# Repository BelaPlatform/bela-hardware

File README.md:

# Bela Hardware

This repo contains the editable hardware design files for Bela products, including Bela, Bela Mini, Bela accessories.

These PCB designs have been created in and are editable with Cadsoft EAGLE (https://cadsoft.io) and Kicad (http://kicad.org). 

## Licensing

The hardware designs in this repo are licensed under a Creative Commons Attribution Sharealike license, or [CC-BY-SA](http://creativecommons.org/licenses/by-sa/3.0/). This means you are free edit and use these designs, as long as you agree to supply credit and release your results under the same license. [Read about CC-BY-SA here](http://creativecommons.org/licenses/by-sa/3.0/).

If you want to create a commercial product using the Bela hardware designs and don't want to release it under the same license, you will need a commercial license. Drop us an email at info@bela.io to discuss your project, and we can suggest a commercial license to fit your project's scope and scale.

## Branding

The Bela logo is copyrighted, and is reserved for products made or licensed by the Bela team. If you want to include a Bela logo on your project, we've made a Made With Bela logo just for this. [See this page for details on logo use](https://belaplatform.github.io/bela_sample/src/#logos) and to download the Made With Bela logo.

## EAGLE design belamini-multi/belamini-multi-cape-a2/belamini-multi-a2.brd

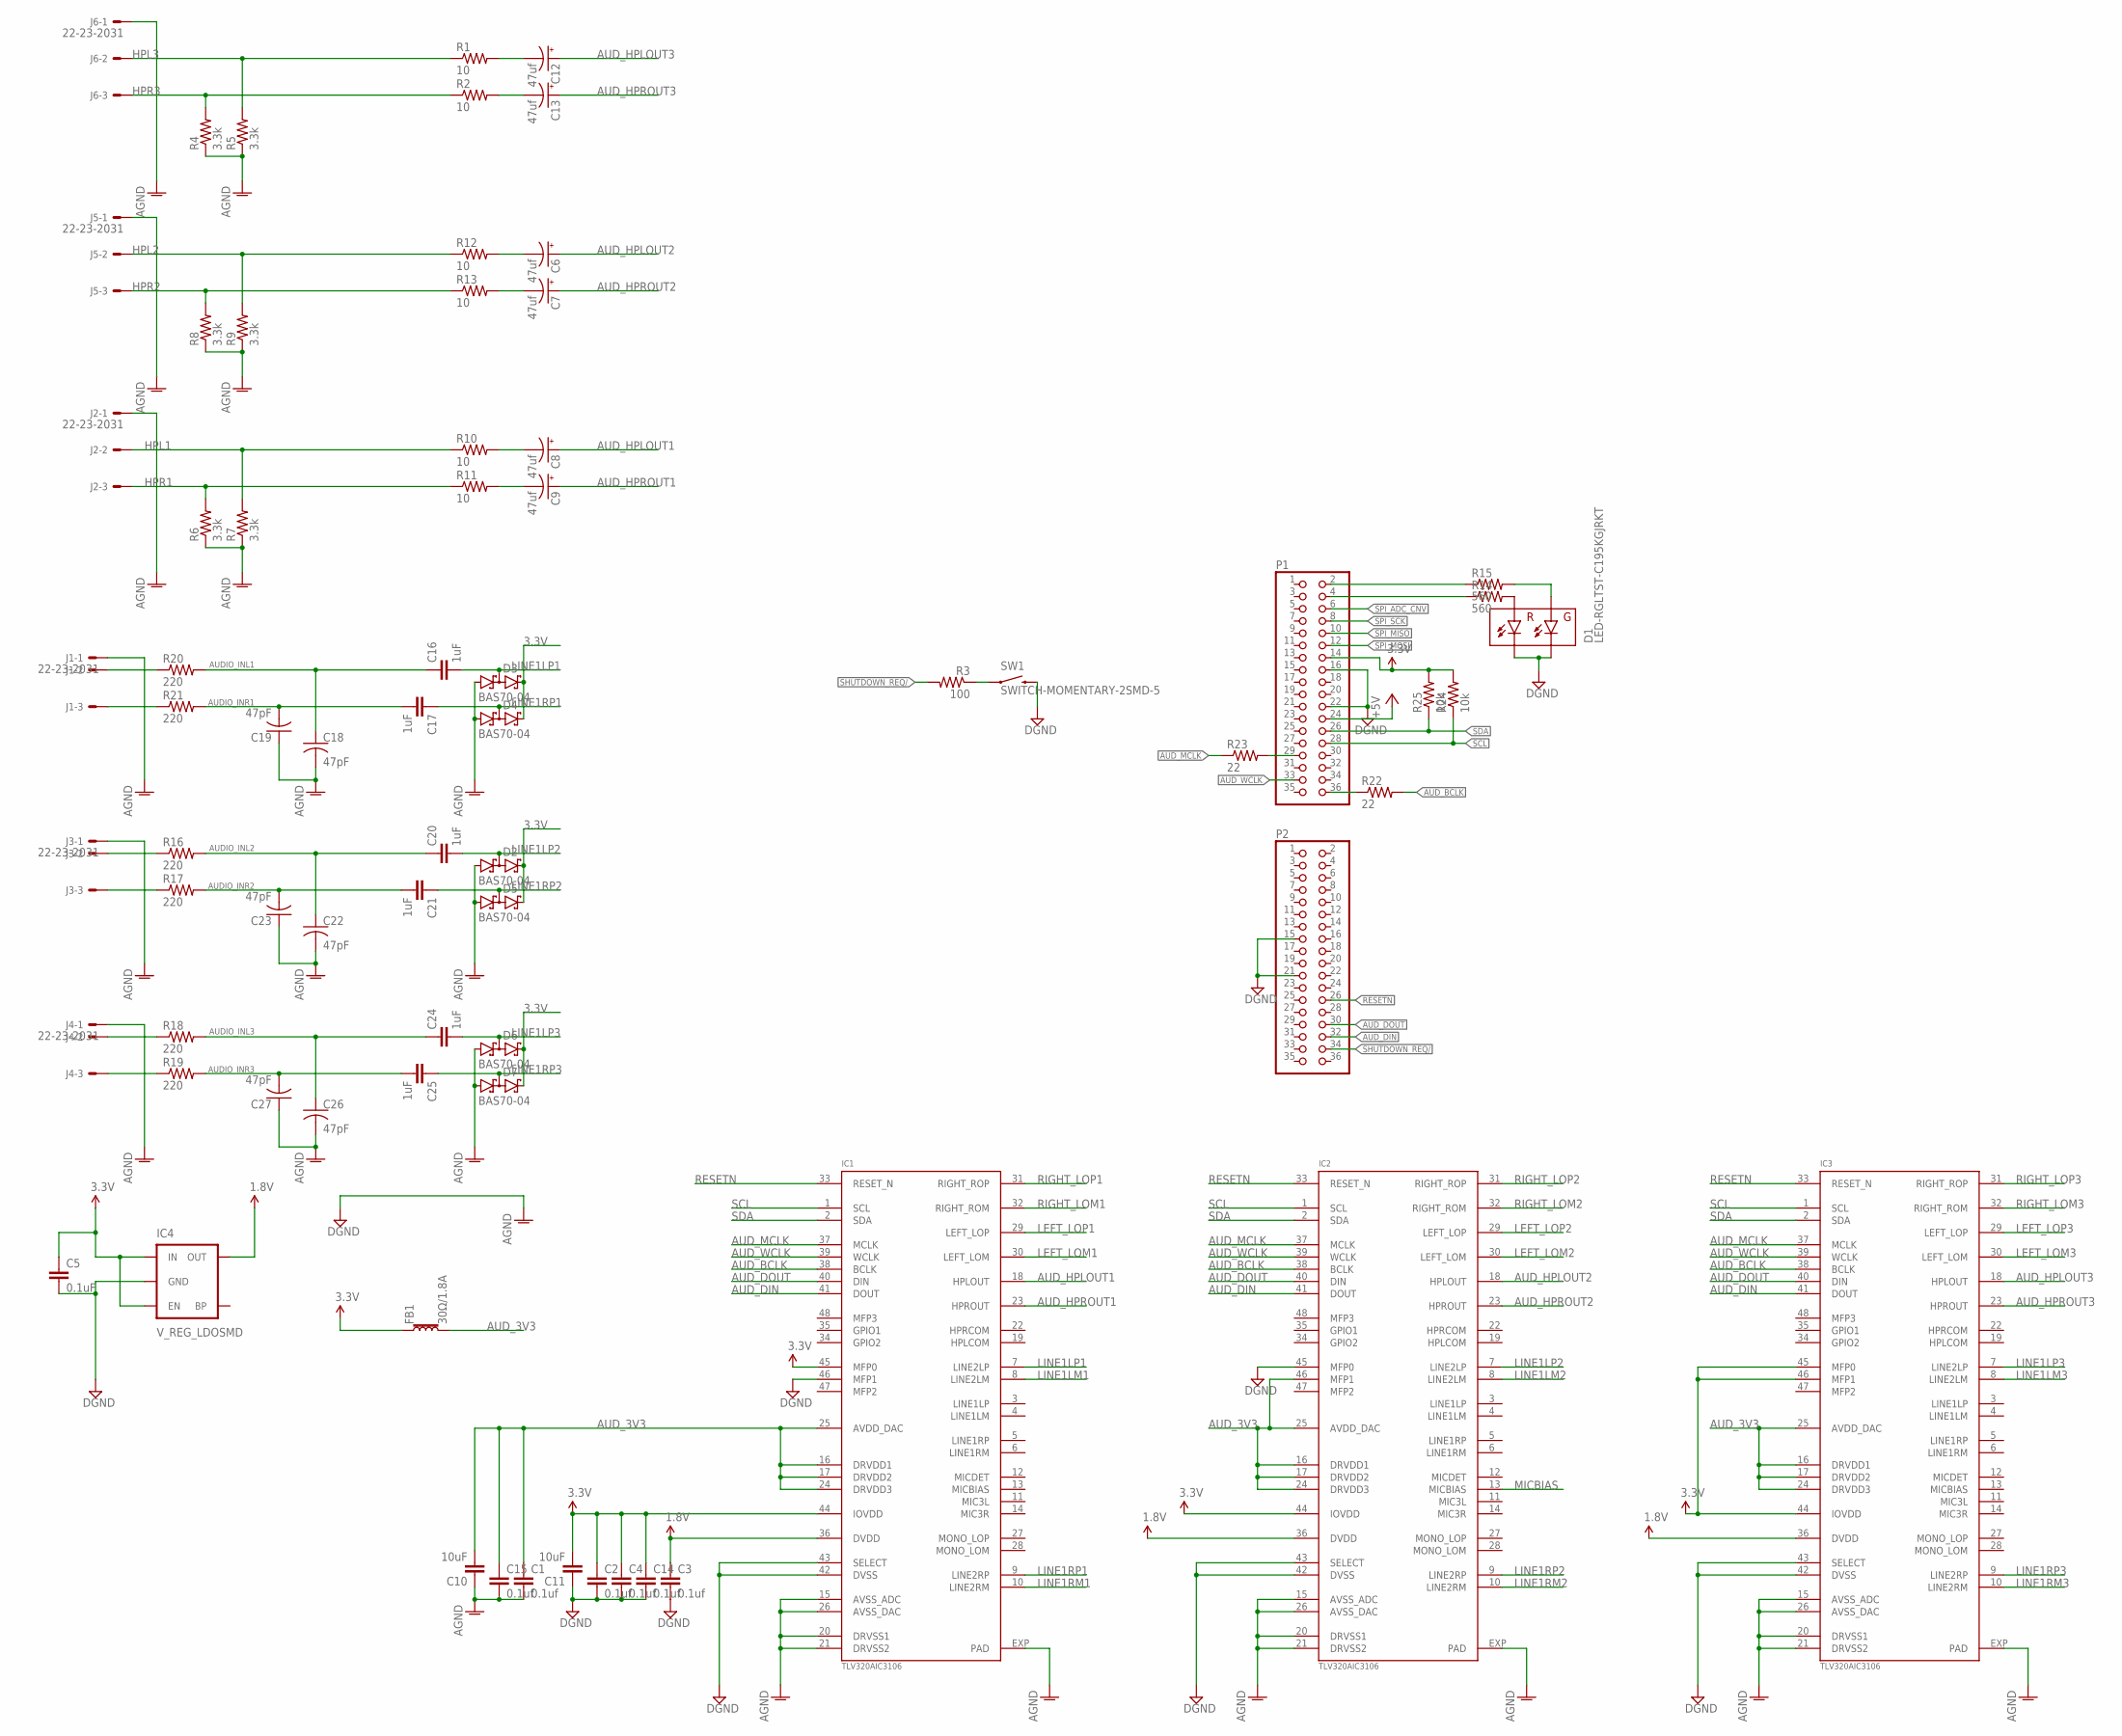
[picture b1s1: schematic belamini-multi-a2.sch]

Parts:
C1, C2, C3, C4, C14, C15: 0.1uf; C0603
C5: 0.1uF; C0603
C6, C7, C8, C9, C12, C13: 47uf; EIA3216
C10, C11: 10uF; 0603-CAP
C16, C17, C20, C21, C24, C25: 1uF; C0603
C18, C19, C22, C23, C26, C27: 47pF; C0402-SMALL
D1: LED-RGLTST-C195KGJRKT; LTST-C195KGJRKT
D2, D3, D4, D5, D6, D7: BAS70-04; SOT23
FB1: 30Ω/1.8A; 0603
IC1, IC2, IC3: TLV320AIC3106; QFN48
IC4: V_REG_LDOSMD; SOT23-5
J1, J2, J3, J4, J5, J6: 22-23-2031
P1, P2: PINHD-2X18; 2X18
R1, R2, R10, R11, R12, R13: 10; C0402-SMALL
R3: 100; C0402-SMALL
R4, R5, R6, R7, R8, R9: 3.3k; C0402-SMALL
R14, R15: 560; C0402-SMALL
R16, R17, R18, R19, R20, R21: 220; C0402-SMALL
R22, R23: 22; C0402-SMALL
R24, R25: 10k; C0402-SMALL
SW1: SWITCH-MOMENTARY-2SMD-5; TACTILE_SWITCH_SMD-4

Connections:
1.8V: C3.1, IC1.36 (DVDD), IC2.36 (DVDD), IC3.36 (DVDD), IC4.5 (OUT)
3.3V: C2.1, C4.1, C5.1, C11.2, C14.1, D2.2 (C2), D3.2 (C2), D4.2 (C2), D5.2 (C2), D6.2 (C2), D7.2 (C2), FB1.1, IC1.44 (IOVDD), IC1.45 (MFP0), IC2.44 (IOVDD), IC3.44 (IOVDD), IC3.45 (MFP0), IC3.46 (MFP1), IC4.1 (IN), IC4.3 (EN), P1.14, R24.P$2 (2), R25.P$2 (2)
+5V: P1.24
AGND: C1.2, C2.2, C3.2, C4.2, C5.2, C10.1, C11.1, C14.2, C15.2, C18.P$2 (2), C19.P$1 (1), C22.P$2 (2), C23.P$1 (1), C26.P$2 (2), C27.P$1 (1), D1.P$3 (GC), D1.P$4 (RC), D2.1 (A1), D3.1 (A1), D4.1 (A1), D5.1 (A1), D6.1 (A1), D7.1 (A1), IC1.15 (AVSS_ADC), IC1.20 (DRVSS1), IC1.21 (DRVSS2), IC1.26 (AVSS_DAC), IC1.42 (DVSS), IC1.43 (SELECT), IC1.46 (MFP1), IC1.EXP (PAD), IC2.15 (AVSS_ADC), IC2.20 (DRVSS1), IC2.21 (DRVSS2), IC2.26 (AVSS_DAC), IC2.42 (DVSS), IC2.43 (SELECT), IC2.45 (MFP0), IC2.EXP (PAD), IC3.15 (AVSS_ADC), IC3.20 (DRVSS1), IC3.21 (DRVSS2), IC3.26 (AVSS_DAC), IC3.42 (DVSS), IC3.43 (SELECT), IC3.EXP (PAD), IC4.2 (GND), J1.1, J2.1, J3.1, J4.1, J5.1, J6.1, P1.16, P1.22, P2.15, P2.21, R4.P$1 (1), R5.P$1 (1), R6.P$1 (1), R7.P$1 (1), R8.P$1 (1), R9.P$1 (1), SW1.4 (2)
AUDIO_INL1: C16.1, C18.P$1 (1), R20.P$2 (2)
AUDIO_INL2: C20.1, C22.P$1 (1), R16.P$2 (2)
AUDIO_INL3: C24.1, C26.P$1 (1), R18.P$2 (2)
AUDIO_INR1: C17.2, C19.P$2 (2), R21.P$2 (2)
AUDIO_INR2: C21.2, C23.P$2 (2), R17.P$2 (2)
AUDIO_INR3: C25.2, C27.P$2 (2), R19.P$2 (2)
AUD_3V3: C1.1, C10.2, C15.1, FB1.2, IC1.16 (DRVDD1), IC1.17 (DRVDD2), IC1.24 (DRVDD3), IC1.25 (AVDD_DAC), IC2.16 (DRVDD1), IC2.17 (DRVDD2), IC2.24 (DRVDD3), IC2.25 (AVDD_DAC), IC2.46 (MFP1), IC3.16 (DRVDD1), IC3.17 (DRVDD2), IC3.24 (DRVDD3), IC3.25 (AVDD_DAC)
AUD_BCLK: IC1.38 (BCLK), IC2.38 (BCLK), IC3.38 (BCLK), R22.P$2 (2)
AUD_DIN: IC1.41 (DOUT), IC2.41 (DOUT), IC3.41 (DOUT), P2.32
AUD_DOUT: IC1.40 (DIN), IC2.40 (DIN), IC3.40 (DIN), P2.30
AUD_HPLOUT1: C8.A (+), IC1.18 (HPLOUT)
AUD_HPLOUT2: C6.A (+), IC2.18 (HPLOUT)
AUD_HPLOUT3: C12.A (+), IC3.18 (HPLOUT)
AUD_HPROUT1: C9.A (+), IC1.23 (HPROUT)
AUD_HPROUT2: C7.A (+), IC2.23 (HPROUT)
AUD_HPROUT3: C13.A (+), IC3.23 (HPROUT)
AUD_MCLK: IC1.37 (MCLK), IC2.37 (MCLK), IC3.37 (MCLK), R23.P$1 (1)
AUD_WCLK: IC1.39 (WCLK), IC2.39 (WCLK), IC3.39 (WCLK), P1.33
HPL1: J2.2, R7.P$2 (2), R10.P$1 (1)
HPL2: J5.2, R9.P$2 (2), R12.P$1 (1)
HPL3: J6.2, R1.P$1 (1), R5.P$2 (2)
HPR1: J2.3, R6.P$2 (2), R11.P$1 (1)
HPR2: J5.3, R8.P$2 (2), R13.P$1 (1)
HPR3: J6.3, R2.P$1 (1), R4.P$2 (2)
LEFT_LOM1: IC1.30 (LEFT_LOM)
LEFT_LOM2: IC2.30 (LEFT_LOM)
LEFT_LOM3: IC3.30 (LEFT_LOM)
LEFT_LOP1: IC1.29 (LEFT_LOP)
LEFT_LOP2: IC2.29 (LEFT_LOP)
LEFT_LOP3: IC3.29 (LEFT_LOP)
LINE1LM1: IC1.8 (LINE2LM)
LINE1LM2: IC2.8 (LINE2LM)
LINE1LM3: IC3.8 (LINE2LM)
LINE1LP1: C16.2, D3.3 (C1A2), IC1.7 (LINE2LP)
LINE1LP2: C20.2, D2.3 (C1A2), IC2.7 (LINE2LP)
LINE1LP3: C24.2, D6.3 (C1A2), IC3.7 (LINE2LP)
LINE1RM1: IC1.10 (LINE2RM)
LINE1RM2: IC2.10 (LINE2RM)
LINE1RM3: IC3.10 (LINE2RM)
LINE1RP1: C17.1, D4.3 (C1A2), IC1.9 (LINE2RP)
LINE1RP2: C21.1, D5.3 (C1A2), IC2.9 (LINE2RP)
LINE1RP3: C25.1, D7.3 (C1A2), IC3.9 (LINE2RP)
MICBIAS: IC2.13 (MICBIAS)
unnamed: J1.2, R20.P$1 (1)
unnamed: C6.C (-), R12.P$2 (2)
unnamed: C7.C (-), R13.P$2 (2)
unnamed: J1.3, R21.P$1 (1)
unnamed: J3.2, R16.P$1 (1)
unnamed: D1.P$2 (RA), R14.P$2 (2)
unnamed: J3.3, R17.P$1 (1)
unnamed: C12.C (-), R1.P$2 (2)
unnamed: J4.2, R18.P$1 (1)
unnamed: C13.C (-), R2.P$2 (2)
unnamed: J4.3, R19.P$1 (1)
unnamed: D1.P$1 (GA), R15.P$2 (2)
unnamed: P1.4, R14.P$1 (1)
unnamed: P1.2, R15.P$1 (1)
unnamed: P1.29, R23.P$2 (2)
unnamed: P1.36, R22.P$1 (1)
unnamed: C8.C (-), R10.P$2 (2)
unnamed: R3.P$1 (1), SW1.1
unnamed: C9.C (-), R11.P$2 (2)
RESETN: IC1.33 (RESET_N), IC2.33 (RESET_N), IC3.33 (RESET_N), P2.26
RIGHT_LOM1: IC1.32 (RIGHT_ROM)
RIGHT_LOM2: IC2.32 (RIGHT_ROM)
RIGHT_LOM3: IC3.32 (RIGHT_ROM)
RIGHT_LOP1: IC1.31 (RIGHT_ROP)
RIGHT_LOP2: IC2.31 (RIGHT_ROP)
RIGHT_LOP3: IC3.31 (RIGHT_ROP)
SCL: IC1.1 (SCL), IC2.1 (SCL), IC3.1 (SCL), P1.28, R24.P$1 (1)
SDA: IC1.2 (SDA), IC2.2 (SDA), IC3.2 (SDA), P1.26, R25.P$1 (1)
SHUTDOWN_REQ/: P2.34, R3.P$2 (2)
SPI_ADC_CNV: P1.6
SPI_MISO: P1.10
SPI_MOSI: P1.12
SPI_SCK: P1.8

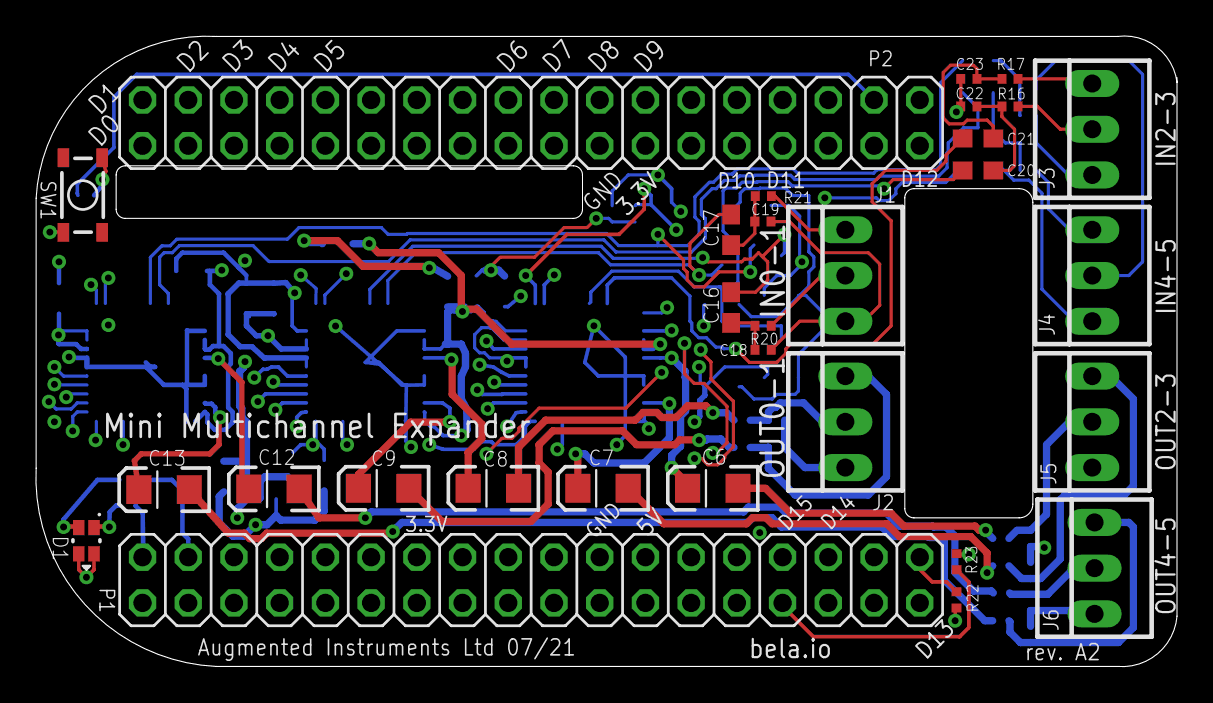
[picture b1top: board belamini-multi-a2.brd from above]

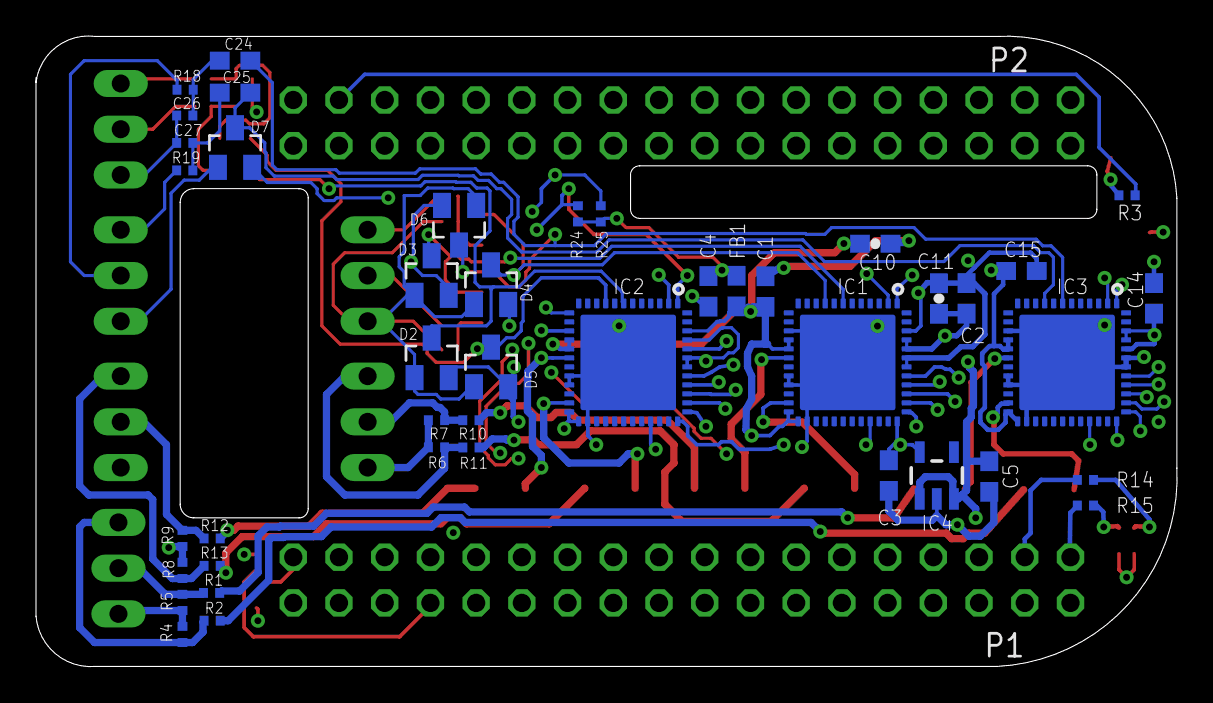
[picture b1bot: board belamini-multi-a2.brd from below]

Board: 4 copper layers, 63.4 x 35.0 mm, 73 parts (43 on the bottom side), 56 nets.

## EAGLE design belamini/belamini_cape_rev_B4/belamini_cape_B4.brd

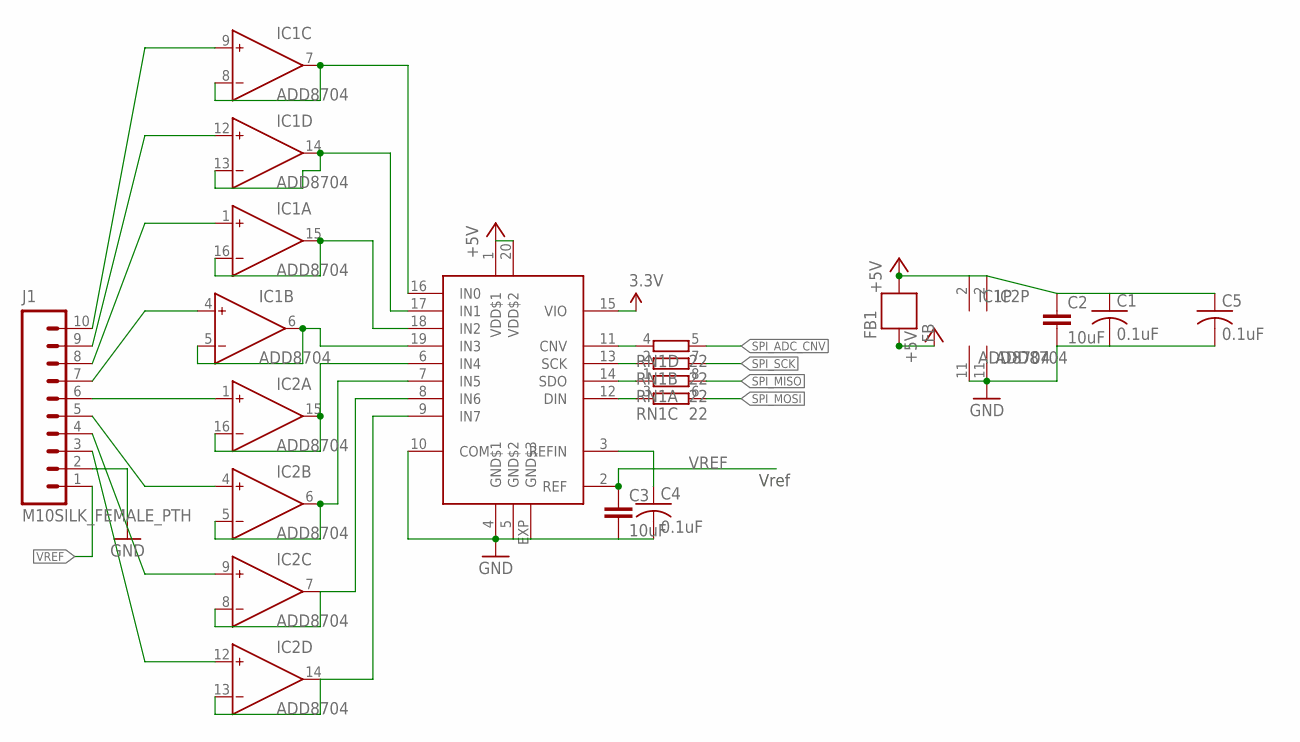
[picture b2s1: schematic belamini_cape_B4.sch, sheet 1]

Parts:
C1, C4, C5: 0.1uF; C0603
C2, C3: 10uF; 0603-CAP
FB1: FB; 0603
IC1, IC2: ADD8704; QFN16-3X3
IC3: AD7699; LFCSP20-LEADS
J1: M10SILK_FEMALE_PTH; 1X10
RN1: 22; 0603-ARC

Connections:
3.3V: IC3.15 (VIO); also elsewhere on the board
+5V_ADC_DAC: C1.1, C2.1, C5.1, FB1.1, IC1.2 (V+), IC2.2 (V+), IC3.1 (VDD$1), IC3.20 (VDD$2)
+5V_SYS: FB1.2; also elsewhere on the board
GND: C1.2, C2.2, C3.2, C4.2, C5.2, IC1.11 (V-), IC2.11 (V-), IC3.4 (GND$1), IC3.5 (GND$2), IC3.10 (COM), IC3.EXP (GND$3), J1.2; also elsewhere on the board
unnamed: IC2.1 (IN+), J1.6
unnamed: IC1.7 (OUT), IC1.8 (IN-), IC3.16 (IN0)
unnamed: IC1.13 (IN-), IC1.14 (OUT), IC3.17 (IN1)
unnamed: IC2.15 (OUT), IC2.16 (IN-), IC3.6 (IN4)
unnamed: IC2.5 (IN-), IC2.6 (OUT), IC3.7 (IN5)
unnamed: IC2.7 (OUT), IC2.8 (IN-), IC3.8 (IN6)
unnamed: IC2.13 (IN-), IC2.14 (OUT), IC3.9 (IN7)
unnamed: IC3.11 (CNV), RN1.4 (1)
unnamed: IC3.12 (DIN), RN1.3 (1)
unnamed: C4.1, IC3.3 (REFIN)
unnamed: IC3.13 (SCK), RN1.2 (1)
unnamed: IC3.14 (SDO), RN1.1
unnamed: IC1.5 (IN-), IC1.6 (OUT), IC3.19 (IN3)
unnamed: IC1.15 (OUT), IC1.16 (IN-), IC3.18 (IN2)
unnamed: IC1.9 (IN+), J1.10
unnamed: IC1.12 (IN+), J1.9
unnamed: IC1.1 (IN+), J1.8
unnamed: IC1.4 (IN+), J1.7
unnamed: IC2.4 (IN+), J1.5
unnamed: IC2.9 (IN+), J1.4
unnamed: IC2.12 (IN+), J1.3
SPI_ADC_CNV: RN1.5 (2); also elsewhere on the board
SPI_MISO: RN1.8 (2); also elsewhere on the board
SPI_MOSI: RN1.6 (2); also elsewhere on the board
SPI_SCK: RN1.7 (2); also elsewhere on the board
VREF: C3.1, IC3.2 (REF), J1.1

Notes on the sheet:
Vref

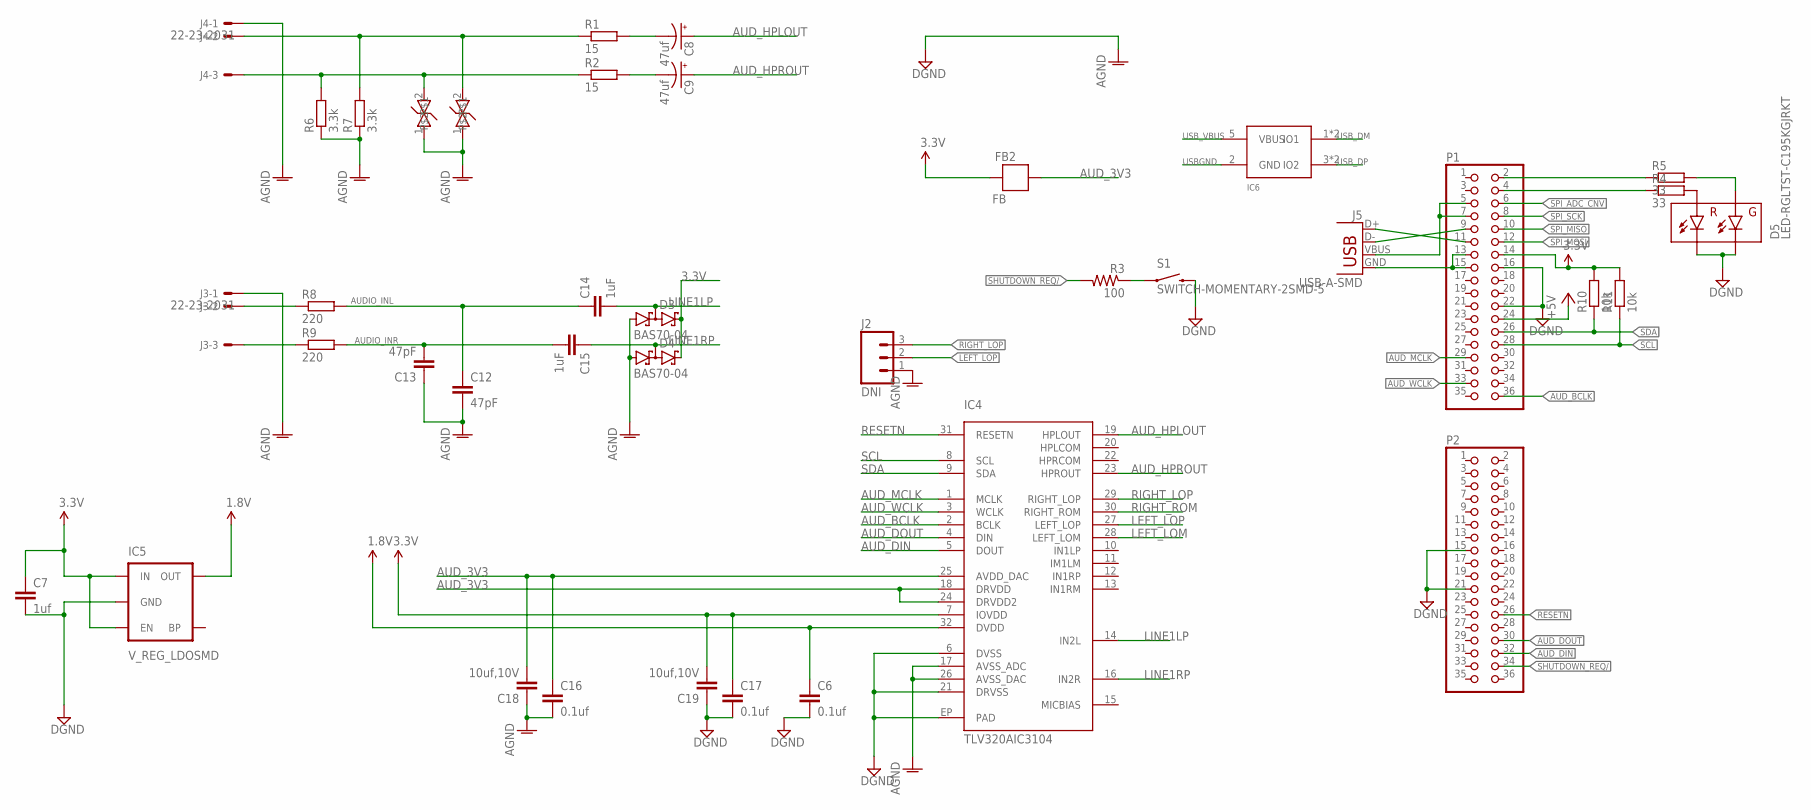
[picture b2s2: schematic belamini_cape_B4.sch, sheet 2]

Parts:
C6, C16, C17: 0.1uf; C0603
C7: 1uf; C0603
C8, C9: 47uf; EIA3216
C12, C13: 47pF; C0603
C14, C15: 1uF; C0603
C18, C19: 10uf,10V; 0603-CAP
D1, D2: PGB0010603MR; 0603
D3, D4: BAS70-04; SOT23
D5: LED-RGLTST-C195KGJRKT; LTST-C195KGJRKT
FB2: FB; 0603
IC4: TLV320AIC3104; QFN-32
IC5: V_REG_LDOSMD; SOT23-5
IC6: USBLC6-2; SOT23-6
J2: DNI; 1X03
J3, J4: 22-23-2031
J5: USB-A-SMD; USB-A-S-NOSILK-FEMALE
P1, P2: PINHD-2X18; 2X18
R1, R2: 15; R0603
R3: 100; R0603
R4, R5: 33; R0603
R6, R7: 3.3k; R0603
R8, R9: 220; R0603
R10, R11: 10k; R0603
S1: SWITCH-MOMENTARY-2SMD-5; TACTILE_SWITCH_SMD-4

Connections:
1.8V: C6.1, IC4.32 (DVDD), IC5.5 (OUT)
3.3V: C7.1, C17.1, C19.2, D3.2 (C2), D4.2 (C2), FB2.2, IC4.7 (IOVDD), IC5.1 (IN), IC5.3 (EN), P1.14, R10.2, R11.2; also elsewhere on the board
+5V_SYS: P1.24; also elsewhere on the board
AUDIO_INL: C12.1, C14.1, R8.2
AUDIO_INR: C13.2, C15.2, R9.2
AUD_3V3: C16.1, C18.2, FB2.1, IC4.18 (DRVDD), IC4.24 (DRVDD2), IC4.25 (AVDD_DAC)
AUD_BCLK: IC4.2 (BCLK), P1.36
AUD_DIN: IC4.5 (DOUT), P2.32
AUD_DOUT: IC4.4 (DIN), P2.30
AUD_HPLOUT: C8.A (+), IC4.19 (HPLOUT)
AUD_HPROUT: C9.A (+), IC4.23 (HPROUT)
AUD_MCLK: IC4.1 (MCLK), P1.29
AUD_WCLK: IC4.3 (WCLK), P1.33
GND: C6.2, C7.2, C12.2, C13.1, C16.2, C17.2, C18.1, C19.1, D1.1, D2.1, D3.1 (A1), D4.1 (A1), D5.P$3 (GC), D5.P$4 (RC), IC4.6 (DVSS), IC4.17 (AVSS_ADC), IC4.21 (DRVSS), IC4.26 (AVSS_DAC), IC4.EP (PAD), IC5.2 (GND), J2.1, J3.1, J4.1, P1.16, P1.22, P2.15, P2.21, R6.1, R7.1, S1.4 (2); also elsewhere on the board
HPL: D2.2, J4.2, R1.1, R7.2
HPR: D1.2, J4.3, R2.1, R6.2
LEFT_LOM: IC4.28 (LEFT_LOM)
LEFT_LOP: IC4.27 (LEFT_LOP), J2.2
LINE1LP: C14.2, D3.3 (C1A2), IC4.14 (IN2L)
LINE1RP: C15.1, D4.3 (C1A2), IC4.16 (IN2R)
unnamed: J3.2, R8.1
unnamed: J3.3, R9.1
unnamed: D5.P$2 (RA), R4.2
unnamed: D5.P$1 (GA), R5.2
unnamed: P1.4, R4.1
unnamed: P1.2, R5.1
unnamed: C8.C (-), R1.2
unnamed: R3.1, S1.1
unnamed: C9.C (-), R2.2
RESETN: IC4.31 (RESETN), P2.26
RIGHT_LOP: IC4.29 (RIGHT_LOP), J2.3
RIGHT_ROM: IC4.30 (RIGHT_ROM)
SCL: IC4.8 (SCL), P1.28, R11.1
SDA: IC4.9 (SDA), P1.26, R10.1
SHUTDOWN_REQ/: P2.34, R3.2
SPI_ADC_CNV: P1.6; also elsewhere on the board
SPI_MISO: P1.10; also elsewhere on the board
SPI_MOSI: P1.12; also elsewhere on the board
SPI_SCK: P1.8; also elsewhere on the board
USBGND: IC6.2 (GND), J5.GND, P1.13, P1.15
USB_DM: IC6.1 (IO1), IC6.6 (IO1), J5.D-, P1.9
USB_DP: IC6.3 (IO2), IC6.4 (IO2), J5.D+, P1.11
USB_VBUS: IC6.5 (VBUS), J5.VBUS, P1.5, P1.7

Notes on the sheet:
IC6

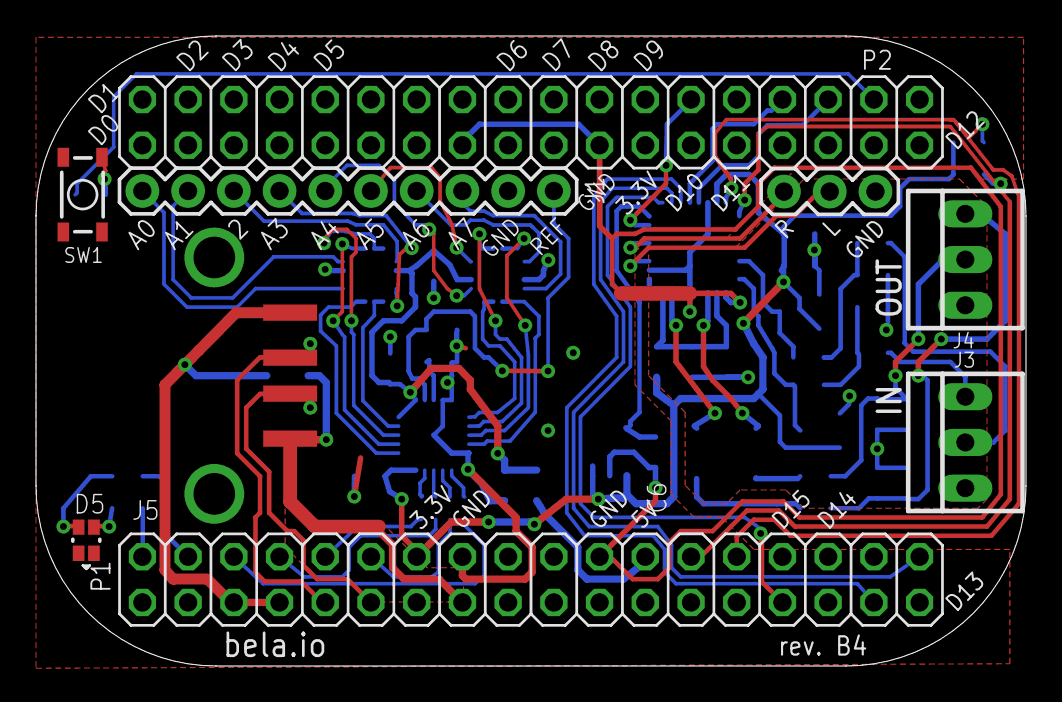
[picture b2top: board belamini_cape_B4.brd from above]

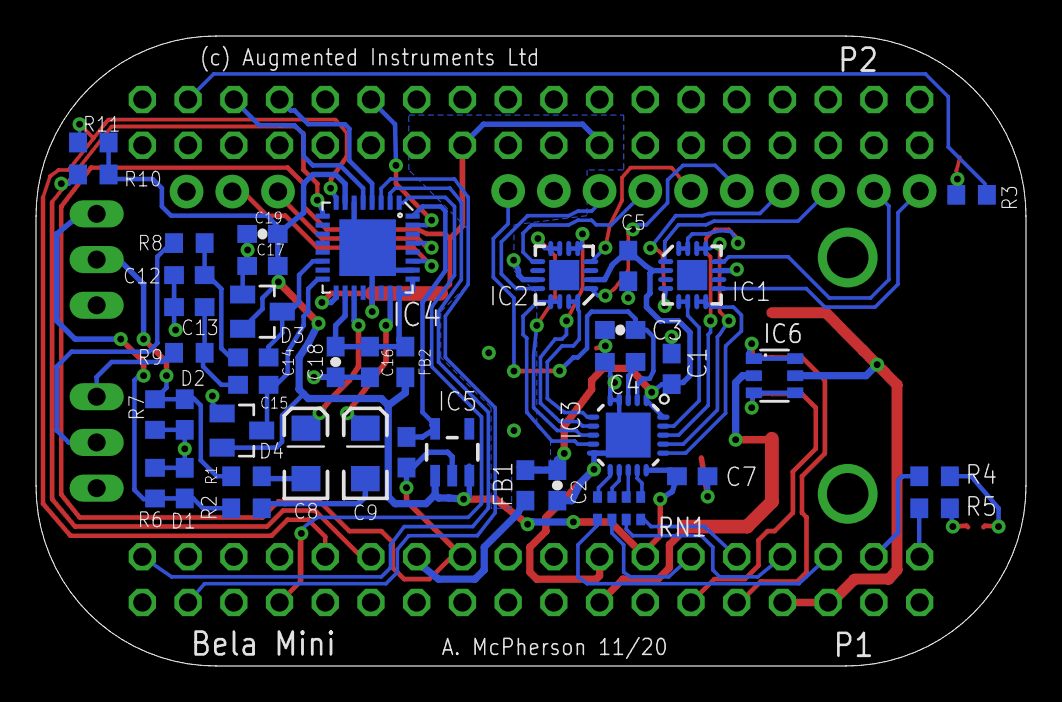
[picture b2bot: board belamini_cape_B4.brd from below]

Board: 2 copper layers, 55.0 x 35.0 mm, 50 parts (41 on the bottom side), 64 nets.

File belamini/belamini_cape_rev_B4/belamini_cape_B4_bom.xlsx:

Name | Quantity | Value | Side | Package | Description | Farnell # | Mouser # | Datasheet / Notes
 |  |  |  |  |  |  | 810-C1608X5R1A106M
C2, C3, C18, C19 | 4 | 10uF | bottom | “0603” | Capacitor ceramic 0603 | 2309028
C7, C14, C15 | 3 | 1uF | bottom | “0603” | Capacitor ceramic 0603 | 2496916 | 77-VJ0603V105MXQPBC
C1, C4, C5, C6, C16, C17 | 6 | 0.1uF | bottom | “0603” | Capacitor ceramic 0603 | 1709957 | 80-C0603C104K5R
C12, C13 | 2 | 47pF | bottom | "0603" | Capacitor ceramic 0603 | 1759062 | 77-VJ0603A470JXACBC
C8, C9 | 2 | 47uF | bottom | "1206" | Capacitor electrolytic 1206 | 2353044 | 647-F930J476MAA
C10, C11 | 0 | DNI (removed from design)
D1, D2 | 2 | TE Connectivity PESD0603-240 | bottom | "0603" | ESD suppressor 24V |  | 650-PESD0603-240
D3, D4 | 2 | BAS70-04 | bottom | SOT23-3 | Dual Schottky diode |  | 863-BAS70-04LT1G |  |  |  |  |  | D3, D4
D5 | 1 | Lite-On LTST-C195TBJRKT | top | “0606” | blue/red LED |  | 859-LTST-C195TBJRKT | Important: check pinout of any generic equivalent part. Dot indicates the negat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
FB1, FB2 | 4 | Ferrite bead | bottom | “0603” | Ferrite bead 0603 | 1781090 | 810-MPZ1608S121A
IC1, IC2 | 2 | TSV524 | bottom | QFN-16 | Quad op-amp |  | 511-TSV524IQ4T
IC3 | 1 | AD7699 | bottom | LFCSP-20 | 16-bit ADC |  | 584-AD7699BCPZ
IC4 | 1 | TLV320AIC3104 | bottom | QFN-32 | Audio codec |  | 595-TLV320C3104IRHBR
IC5 | 1 | MIC5317 | bottom | SOT23-5 | 1.8V regulator |  | 998-MIC5317-1.8YM5TR
IC6 | 1 | USBLC6-2SC6 | bottom | SOT23-6 | ESD suppressor for USB |  | 511-USBLC6-2SC6
J1 | 1 | 10-pin socket | top | Through Hole | 10-pin socket |  | 992-10FX1-254MM
J2 | 1 | 3-pin header | top | Through Hole | 3-pin socket |  | 855-M20-7820346
J3, J4 | 2 | Molex 3-pin | top | Through Hole | 3-pin Molex KK series connector |  | 538-22-23-2031
J5 | 1 | Amphenol 87583-3010RPALF | top | Solder Pad | USB A socket, solder pad | 1314363 | 649-87583-3010RPALF
P1, P2 | 2 | 36-pin header | top | Through Hole | 2x18 2.54mm stacking headers (10mm male pins on bottom, female sockets on top). |  |  | Important: use 10mm pin length rather than 12.5mm used on previous Bela builds
R1, R2 | 2 | 15 ohm | bottom | “0603” | Resistor 0603
R3 | 1 | 100 ohm | bottom | “0603” | Resistor 0603
R4, R5 | 2 | 560 ohm | bottom | “0603” | Resistor 0603
R6, R7 | 2 | 3.3k ohm | bottom | “0603” | Resistor 0603
R8, R9 | 2 | 220 ohm | bottom | “0603” | Resistor 0603
R10, R11 | 2 | 10k ohm | bottom | “0603” | Resistor 0603
RN1 | 1 | 22 ohm 4x network | bottom | “0603” | Resistor network 4x0603 | 2060086
S1 | 1 | C&K Components PTS810 SJG 250 SMTR LFS | top | SMD | Micro tactile switch |  | 611-PTS810SJG250SMTR
Total | 52
BOM rev. B4

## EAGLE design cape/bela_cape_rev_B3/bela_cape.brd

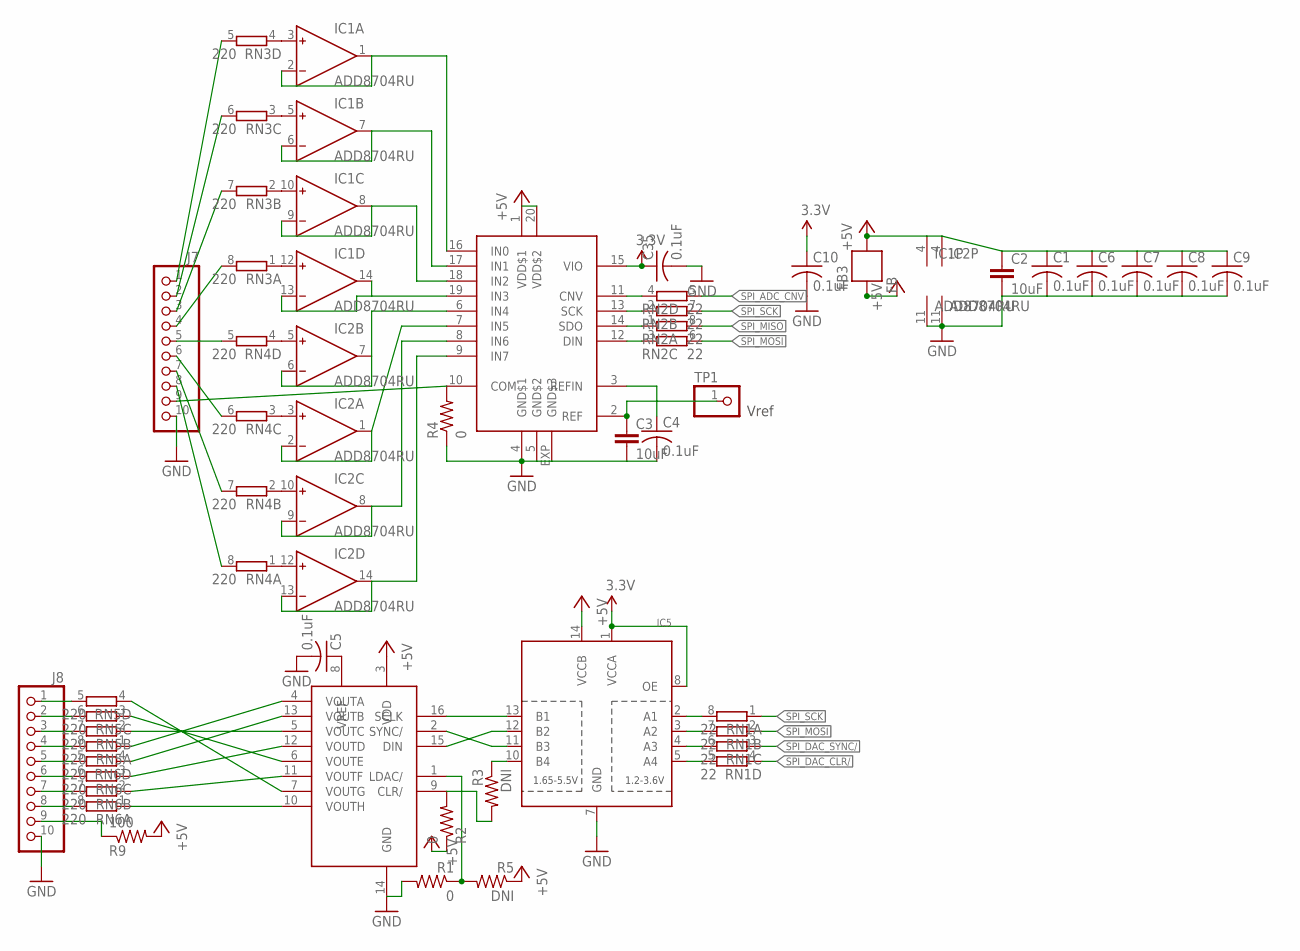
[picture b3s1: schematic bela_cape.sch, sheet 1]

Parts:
C1, C4, C5, C6, C7, C8, C9, C10, C35: 0.1uF; C0603
C2, C3: 10uF; 0603-CAP
FB3: FB; 0603
IC1, IC2: ADD8704RU; TSSOP14
IC3: AD5668; TSSOP16-PW
IC4: AD7699; LFCSP20-LEADS
IC5: TXB0104PWR; TSSOP14
J7, J8: PINHD-1X10; 1X10
R1, R2, R4: 0; R0603
R3, R5: DNI; R0603
R9: 100; R0603
RN1, RN2: 22; 0603-ARC
RN3, RN4, RN5, RN6: 220; 0603-ARC
TP1: PINHD-1X1; 1X01

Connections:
3.3V: C10.1, C35.1, IC4.15 (VIO), IC5.1 (VCCA), IC5.8 (OE); also elsewhere on the board
+5V_ADC_DAC: C1.1, C2.1, C6.1, C7.1, C8.1, C9.1, FB3.1, IC1.4 (V+), IC2.4 (V+), IC3.3 (VDD), IC4.1 (VDD$1), IC4.20 (VDD$2), IC5.14 (VCCB), R2.1, R5.1, R9.2
+5V_SYS: FB3.2; also elsewhere on the board
DGND: C1.2, C2.2, C3.2, C4.2, C5.2, C6.2, C7.2, C8.2, C9.2, C10.2, C35.2, IC1.11 (V-), IC2.11 (V-), IC3.14 (GND), IC4.4 (GND$1), IC4.5 (GND$2), IC4.EXP (GND$3), IC5.7 (GND), J7.10, J8.10, R1.2, R4.1; also elsewhere on the board
unnamed: IC3.16 (SCLK), IC5.13 (B1)
unnamed: IC3.15 (DIN), IC5.12 (B2)
unnamed: IC3.2 (SYNC/), IC5.11 (B3)
unnamed: IC3.9 (CLR/), R2.2, R3.2
unnamed: IC1.1 (OUT), IC1.2 (IN-), IC4.16 (IN0)
unnamed: IC1.6 (IN-), IC1.7 (OUT), IC4.17 (IN1)
unnamed: IC1.8 (OUT), IC1.9 (IN-), IC4.18 (IN2)
unnamed: IC1.13 (IN-), IC1.14 (OUT), IC4.19 (IN3)
unnamed: IC2.1 (OUT), IC2.2 (IN-), IC4.7 (IN5)
unnamed: IC2.6 (IN-), IC2.7 (OUT), IC4.6 (IN4)
unnamed: IC2.8 (OUT), IC2.9 (IN-), IC4.8 (IN6)
unnamed: IC2.13 (IN-), IC2.14 (OUT), IC4.9 (IN7)
unnamed: IC5.10 (B4), R3.1
unnamed: IC4.11 (CNV), RN2.4 (1)
unnamed: C5.1, IC3.8 (VREF)
unnamed: IC5.2 (A1), RN1.8 (2)
unnamed: IC5.3 (A2), RN1.7 (2)
unnamed: IC5.4 (A3), RN1.6 (2)
unnamed: IC5.5 (A4), RN1.5 (2)
unnamed: IC4.12 (DIN), RN2.3 (1)
unnamed: C3.1, IC4.2 (REF), TP1.1
unnamed: C4.1, IC4.3 (REFIN)
unnamed: IC4.13 (SCK), RN2.2 (1)
unnamed: IC4.14 (SDO), RN2.1
unnamed: IC4.10 (COM), J7.9, R4.2
unnamed: IC1.3 (IN+), RN3.4 (1)
unnamed: IC1.5 (IN+), RN3.3 (1)
unnamed: IC1.10 (IN+), RN3.2 (1)
unnamed: IC1.12 (IN+), RN3.1
unnamed: IC2.5 (IN+), RN4.4 (1)
unnamed: IC2.3 (IN+), RN4.3 (1)
unnamed: IC2.10 (IN+), RN4.2 (1)
unnamed: IC2.12 (IN+), RN4.1
unnamed: IC3.1 (LDAC/), R1.1, R5.2
unnamed: J7.1, RN3.5 (2)
unnamed: J7.2, RN3.6 (2)
unnamed: J7.3, RN3.7 (2)
unnamed: J7.4, RN3.8 (2)
unnamed: J7.5, RN4.5 (2)
unnamed: J7.6, RN4.6 (2)
unnamed: J7.7, RN4.7 (2)
unnamed: J7.8, RN4.8 (2)
unnamed: IC3.7 (VOUTG), RN5.4 (1)
unnamed: IC3.6 (VOUTE), RN5.3 (1)
unnamed: IC3.5 (VOUTC), RN5.2 (1)
unnamed: IC3.4 (VOUTA), RN5.1
unnamed: IC3.13 (VOUTB), RN6.4 (1)
unnamed: IC3.12 (VOUTD), RN6.3 (1)
unnamed: IC3.11 (VOUTF), RN6.2 (1)
unnamed: J8.8, RN6.8 (2)
unnamed: J8.9, R9.1
unnamed: IC3.10 (VOUTH), RN6.1
unnamed: J8.7, RN6.7 (2)
unnamed: J8.6, RN6.6 (2)
unnamed: J8.5, RN6.5 (2)
unnamed: J8.4, RN5.8 (2)
unnamed: J8.3, RN5.7 (2)
unnamed: J8.2, RN5.6 (2)
unnamed: J8.1, RN5.5 (2)
SPI_ADC_CNV: RN2.5 (2); also elsewhere on the board
SPI_DAC_CLR/: RN1.4 (1); also elsewhere on the board
SPI_DAC_SYNC/: RN1.3 (1); also elsewhere on the board
SPI_MISO: RN2.8 (2); also elsewhere on the board
SPI_MOSI: RN1.2 (1), RN2.6 (2); also elsewhere on the board
SPI_SCK: RN1.1, RN2.7 (2); also elsewhere on the board

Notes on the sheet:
Vref

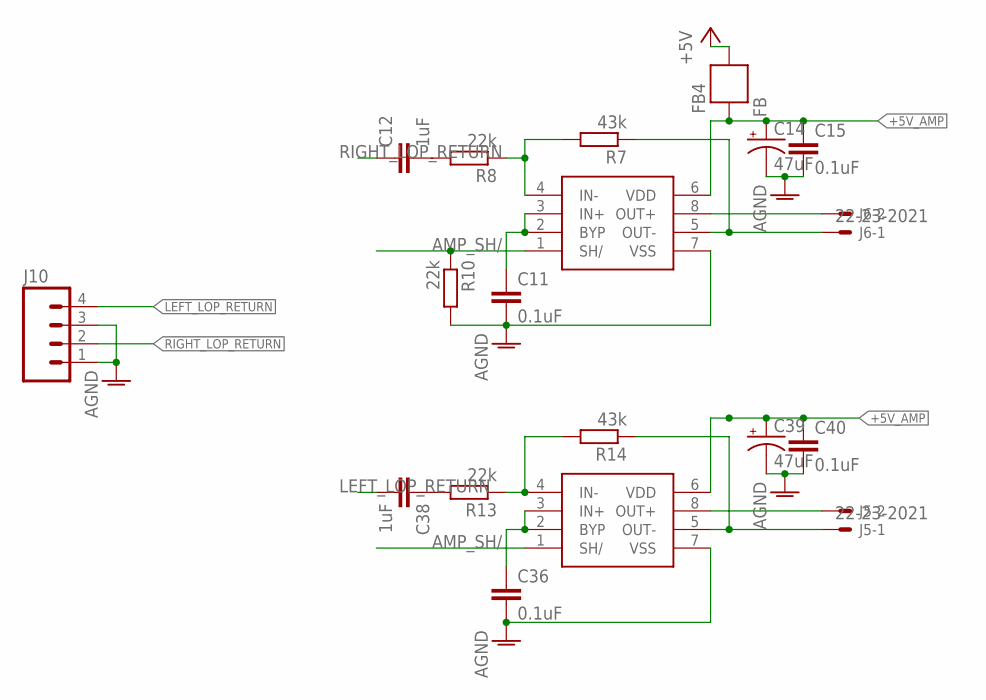
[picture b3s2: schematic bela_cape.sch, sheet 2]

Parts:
C11, C15, C36, C40: 0.1uF; C0603
C12, C38: 1uF; C0603
C14, C39: 47uF; EIA3216
FB4: FB; 0603
IC8, IC9: LM4876; SO8
J5, J6: 22-23-2021
J10: M04PTH; 1X04
R7, R14: 43k; R0603
R8, R10, R13: 22k; R0603

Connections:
+5V_AMP: C14.A (+), C15.1, C39.A (+), C40.1, FB4.2, IC8.6 (VDD), IC9.6 (VDD); also elsewhere on the board
+5V_POW: FB4.1; also elsewhere on the board
AGND: C11.2, C14.C (-), C15.2, C36.2, C39.C (-), C40.2, IC8.7 (VSS), IC9.7 (VSS), J10.1, J10.3, R10.2; also elsewhere on the board
AMP_SH/: IC8.1 (SH/), IC9.1 (SH/), R10.1; also elsewhere on the board
LEFT_LOP_RETURN: C38.2, J10.4
unnamed: IC9.4 (IN-), R13.1, R14.2
unnamed: IC8.4 (IN-), R7.2, R8.1
unnamed: C11.1, IC8.2 (BYP), IC8.3 (IN+)
unnamed: C12.2, R8.2
unnamed: IC8.5 (OUT-), J6.1, R7.1
unnamed: C36.1, IC9.2 (BYP), IC9.3 (IN+)
unnamed: C38.1, R13.2
unnamed: IC9.5 (OUT-), J5.1, R14.1
unnamed: IC9.8 (OUT+), J5.2
unnamed: IC8.8 (OUT+), J6.2
RIGHT_LOP_RETURN: C12.1, J10.2

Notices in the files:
capelets/audio_expander/audio_capelet_A2/audio_capelet.brd:
(c) 2016
parts and their libraries:
SparkFun-Capacitors: Licensing: CC v3.0 Share-Alike You are welcome to use this library for commercial purposes.
SparkFun-LED: Licensing: Creative Commons ShareAlike 4.0 International - https://creativecommons.org/licenses/by-sa/4.0
